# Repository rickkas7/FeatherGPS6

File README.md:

# FeatherGPS6

**Feather with u-blox M8 GNSS for Particle Boron and Argon**

## Hardware

### Schematic and Board Layout

### BoM (Bill of Materials)

| Quantity | Part | Description | Example | Cost | 
| :---: | :--- | :--- | :--- | ---: | 
| 2 | C1, C3 | CAP CER 0.01UF 100V X7R 0603 | [Murata GCM188R72A103KA37J](https://www.digikey.com/product-detail/en/murata-electronics-north-america/GCM188R72A103KA37J/490-8028-1-ND/4380313) | |
| 1 | C2 | CAP CER 0.1UF 25V X7R 0603 | [Samsung CL10B104KA8NNNC](https://www.digikey.com/product-detail/en/samsung-electro-mechanics/CL10B104KA8NNNC/1276-1006-1-ND/3889092) | | 
| 1 | C4 | CAP CER 10UF 16V X5R 0805 | [Murata GRM21BR61C106KE15L](https://www.digikey.com/product-detail/en/murata-electronics-north-america/GRM21BR61C106KE15L/490-3886-1-ND/965928) | |
| 1 | D1 | LED RED CLEAR 0603 SMD | [Lite-On C193KRKT](https://www.digikey.com/product-detail/en/lite-on-inc/LTST-C193KRKT-5A/160-1830-1-ND/2356251) | $0.41 |
| 1 | J1 | CONN SMA JACK R/A 50 OHM PCB | [TE 5-1814400-1](https://www.digikey.com/product-detail/en/te-connectivity-amp-connectors/5-1814400-1/A97593-ND/1755981) | $2.82 |
| 1 | L1 | FIXED IND 27UH 5MA 1 OHM SMD  | [TDK Corporation MLF2012C270KT000](https://www.digikey.com/product-detail/en/tdk-corporation/MLF2012C270KT000/445-1064-1-ND/504462) | $0.18 | 
| 1 | R1 | RES SMD 10 OHM 5% 1/10W 0603 | [Panasonic ERJ-3GEYJ100V](https://www.digikey.com/product-detail/en/panasonic-electronic-components/ERJ-3GEYJ100V/P10GCT-ND/62816) | | 
| 2 | R3, R5 | RES SMD 10K OHM 5% 1/4W 0603 | [Panasonic ERJ-PA3J103V](https://www.digikey.com/product-detail/en/panasonic-electronic-components/ERJ-PA3J103V/P10KBZCT-ND/5036237) | | 
| 1 | R4 | RES SMD 270 OHM 5% 1/10W 0603 | [Panasonic ERJ-3GEYJ271V](https://www.digikey.com/product-detail/en/panasonic-electronic-components/ERJ-3GEYJ271V/P270GCT-ND/134766) | | 
| 1 | U1 | ACCEL 2-16G I2C/SPI 16LGA | [LIS3DHTR](https://www.digikey.com/product-detail/en/stmicroelectronics/LIS3DHTR/497-10613-1-ND/2334355) | $1.53 |
| 1 | U2 | RF RCVR GNSS/GPS 1.575GHZ 18LCC | [u-blox MAX-M8Q-0](https://www.digikey.com/product-detail/en/u-blox-america-inc/MAX-M8Q-0/672-1003-1-ND/6150666) | $21.00 |
| 1 | U3 | IC FRAM 64K I2C 3.4MHZ 8SOP | [Fujitsu MB85RC64TAPNF-G-BDERE1](https://www.digikey.com/product-detail/en/fujitsu-electronics-america-inc/MB85RC64TAPNF-G-BDERE1/865-1274-1-ND/6802280) | $1.58 |
|   |    | Male Header Pins (0.1") | [Sullins PRPC040SAAN-RC](https://www.digikey.com/product-detail/en/PRPC040SAAN-RC/S1011EC-40-ND/2775214) | |

### Differences from Electron AssetTracker V2

While both this board and the Electron AssetTracker V2 have a u-blox MAX M8 GNSS, there are some notable differences:

- There is no built-in GNSS antenna, there is only a SMA connector for an external active antenna.
- The u-blox GNSS is connected by I2C in this board instead of UART serial. Since there is only one hardware serial port available on the Boron and Argon, using I2C frees up ports as I2C can be shared by many peripherals.
- The LIS3DH is connected by I2C instead of SPI. Using I2C frees up the SPI pins and a CS pin.
- This board contains an optional FRAM, ferro-electric non-volatile RAM. You don't need to populate this, but it's handy if you want to store some data that requires more permanence than retained memory but needs to be able to read and written frequently, where flash were would be an issue.
- There is no u-blox GNSS power control MOSFET. The GNSS has a large inrush of current when you power it on, and this will brown out a Boron or Argon and cause the MCU to reset. Instead, the GNSS is powered down in software.
- The LED is not driven by the GNSS TIMEPULSE pin, it's connected to a MCU GPIO (A5). This allows for a more useful status display.

| | Electron AssetTracker V2 LED | FeatherGPS6 LED |
| :--- | :---: | :---: |
| GNSS Off | Off | Off | 
| Scanning for satellites (<= 3 found) | Off | Slow Blink |
| Scanning for satellites (> 3 found) | Off | Fast Blink |
| GNSS lock | Blink | On | 

- The other issues with TIMEPULSE are that it start blinking when GNSS time is locked, which can occur at 4 satellites, before location lock is achieved. This is confusing. Also, when in software power-down, TIMEPULSE is pulled high with a weak pull-up in the GNSS, which causes the LED to be lit dimly when in powerdown mode, which unnecessarily uses power.

## Example Firmware

Full test code source:

```cpp

#include "AssetTrackerRK.h"

SYSTEM_THREAD(ENABLED);

SYSTEM_MODE(SEMI_AUTOMATIC);

SerialLogHandler logHandler;

void checkGnss(); // forward declaration
void buttonHandler(system_event_t event, int param);

const unsigned long PUBLISH_PERIOD = 120000;
const unsigned long SERIAL_PERIOD = 5000;
const unsigned long CHECK_PERIOD = 100;

AssetTrackerFeather6 t;
unsigned long lastCheck = 0;
unsigned long lastSerial = 0;
unsigned long lastPublish = 0;
unsigned long startFix = 0;
bool gettingFix = false;
bool doSleep = false;

void setup()
{
	// When the MODE button is pressed, the device will go to sleep for 
	// 60 seconds.
	System.on(button_final_click, buttonHandler);

	// Optional: Enable this to wait for USB serial to connect so you can
	// see all of the log messages at startup.
	waitFor(Serial.isConnected, 10000);

	// Be sure to call Tracker setup from setup!
	t.setup();

    startFix = millis();
    gettingFix = true;

	Particle.connect();
}

void loop()
{
	// Be sure to call Tracker loop from loop. 
    t.loop();

	checkGnss();

	if (doSleep) {
		doSleep = false;

		Log.info("going to sleep");

		// Put the GPS to sleep
		t.gnssSleep();

		// Put the system to sleep
		SystemSleepConfiguration config;
		config.mode(SystemSleepMode::ULTRA_LOW_POWER)
			.duration(60s);

		System.sleep(config);

		waitFor(Serial.isConnected, 10000);

		Log.info("woke from sleep");

		// Restart the connecting to GNSS timer
		lastSerial = 0;

		// Wake the GPS again
		t.gnssWake();

	}
}

void checkGnss()
{
	if (millis() - lastCheck < CHECK_PERIOD) {
		return;
	}
	lastCheck = millis();

	// Check the GNSS 10 times per second (100 milliseconds)

	char buf[128];
	bool fixStatusChange = false;

	if (t.gpsFix()) {
		snprintf(buf, sizeof(buf), "location:%f,%f altitude:%f satellites:%d hdop:%d", t.readLatDeg(), t.readLonDeg(), t.getAltitude(), t.getSatellites(), t.getTinyGPSPlus()->getHDOP().value());
		if (gettingFix) {
			gettingFix = false;
			fixStatusChange = true;
			unsigned long elapsed = millis() - startFix;
			Log.info("%lu milliseconds to get GPS fix", elapsed);
		}
	}
	else {
		snprintf(buf, sizeof(buf), "no location satellites:%d", t.getSatellites());
		if (!gettingFix) {
			gettingFix = true;
			fixStatusChange = true;
			startFix = millis();
		}
	}

	if (millis() - lastSerial >= SERIAL_PERIOD || fixStatusChange) {
		lastSerial = millis();
		Log.info(buf);
	}

	// Publish to the cloud
	if (Particle.connected()) {
		if (millis() - lastPublish >= PUBLISH_PERIOD) {
			lastPublish = millis();
			Particle.publish("gps", buf, PRIVATE);
		}
	}

}

void buttonHandler(system_event_t event, int param) {
	// int clicks = system_button_clicks(param);

	doSleep = true;
}
```

### Details

This library uses the [**AssetTrackerRK**](https://github.com/rickkas7/AssetTrackerRK) library for managing the GNSS. It also includes the [**LIS3DH**](https://github.com/rickkas7/LIS3DH) library for using the LIS3DH accelerometer.

To test the sleep mode, tap the MODE button. The device will go into ULTRA_LOW_POWER mode for 60 seconds then reconnect. You should be able to reconnect to the GNSS in around 3 seconds because the ephemeris and almanac data should still be valid.

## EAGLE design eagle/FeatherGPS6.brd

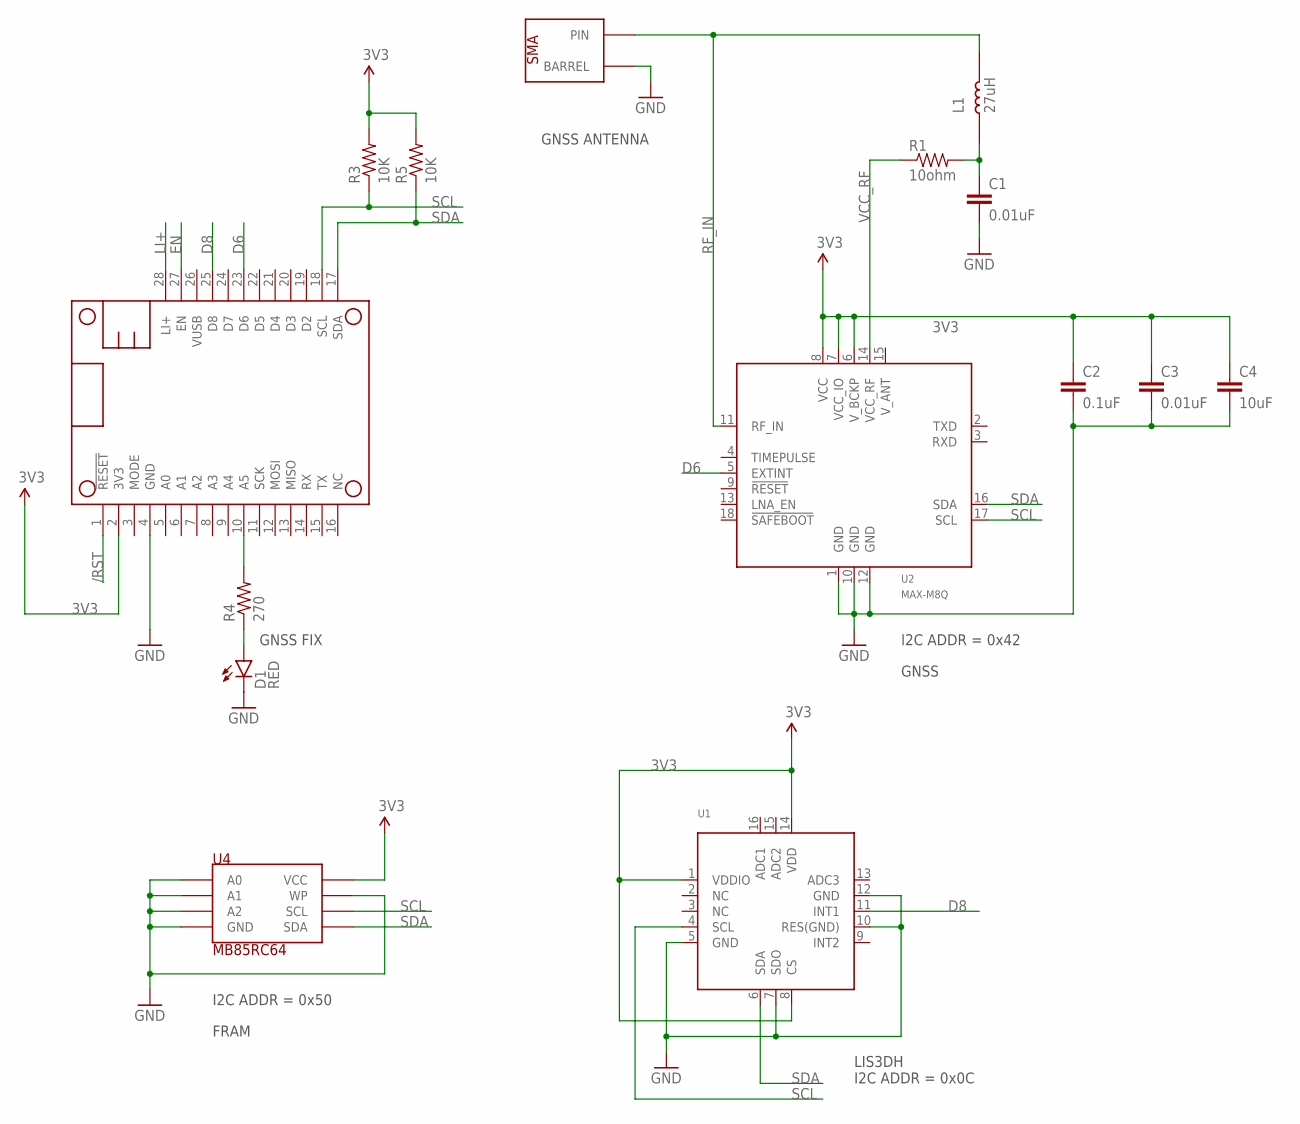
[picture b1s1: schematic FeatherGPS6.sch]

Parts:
C1, C3: 0.01uF; 0603-CAP
C2: 0.1uF; 0603-CAP
C4: 10uF; 0603-CAP
D1: RED; LED-0603
J1: SMA; CONN-SMA
L1: 27uH; 0805
MS1: FEATHERWING_NODIM
R1: 10ohm; 0603-RES
R3, R5: 10K; 0603-RES
R4: 270; 0603-RES
U1: LIS3DHTR; MICROBUILDER_LGA16_3X3MM
U2: MAX-M8Q; U-BLOX_MAX-M8
U4: MB85RC64; 8-SOIC-MAXIM

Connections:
3V3: C2.1, C3.1, C4.1, MS1.2 (3V3), R3.2, R5.2, U1.1 (VDDIO), U1.8 (CS), U1.14 (VDD), U2.6 (V_BCKP), U2.7 (VCC_IO), U2.8 (VCC), U4.8 (VCC)
/RST: MS1.1 (!RESET)
A5: MS1.10 (A5), R4.2
D6: MS1.23 (D6), U2.5 (EXTINT)
D8: MS1.25 (D8), U1.11 (INT1)
EN: MS1.27 (EN)
GND: C1.2, C2.2, C3.2, C4.2, D1.C, J1.2 (BARREL), J1.3 (BARREL), J1.4 (BARREL), J1.5 (BARREL), MS1.4 (GND), U1.5 (GND), U1.7 (SDO), U1.10 (RES(GND)), U1.12 (GND), U2.1 (GND), U2.10 (GND), U2.12 (GND), U4.1 (A0), U4.2 (A1), U4.3 (A2), U4.4 (GND), U4.7 (WP)
LI+: MS1.28 (LI+)
unnamed: C1.1, L1.1, R1.2
unnamed: D1.A, R4.1
RF_IN: J1.PIN, L1.2, U2.11 (RF_IN)
SCL: MS1.18 (SCL), R3.1, U1.4 (SCL), U2.17 (SCL), U4.6 (SCL)
SDA: MS1.17 (SDA), R5.1, U1.6 (SDA), U2.16 (SDA), U4.5 (SDA)
VCC_RF: R1.1, U2.14 (VCC_RF)

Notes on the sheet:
I2C ADDR = 0x42
I2C ADDR = 0x50
GNSS
FRAM
GNSS ANTENNA
GNSS FIX
LIS3DH I2C ADDR = 0x0C

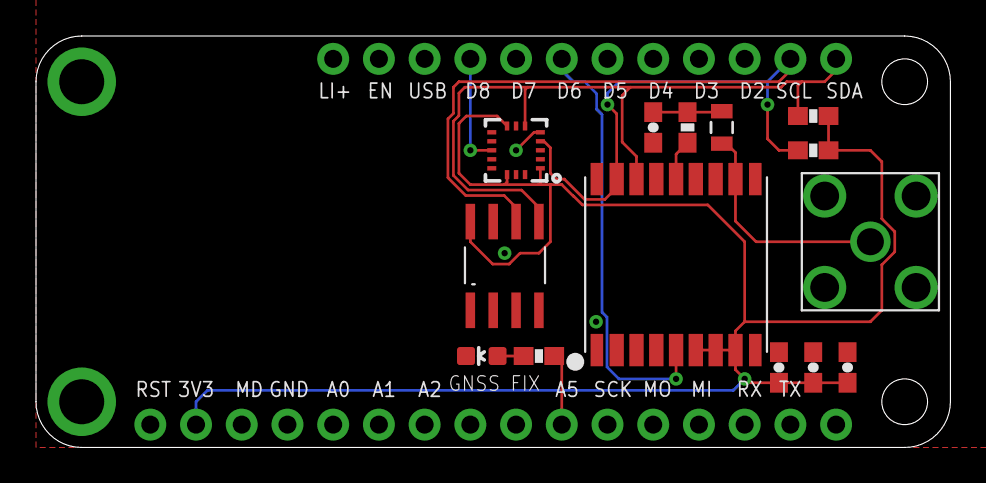
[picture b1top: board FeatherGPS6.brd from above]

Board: 2 copper layers, 50.8 x 22.9 mm, 15 parts (0 on the bottom side), 11 nets.

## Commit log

2020-10-23 Version 0.0.1
    Initial version
